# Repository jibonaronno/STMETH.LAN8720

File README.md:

# STM32ETH.LAN8720
Some standard library files has been customized for test board making simplyfication. A resistor footprint package 0204/7 from resistor.lbr is slightly modyfied.<br>
<br />

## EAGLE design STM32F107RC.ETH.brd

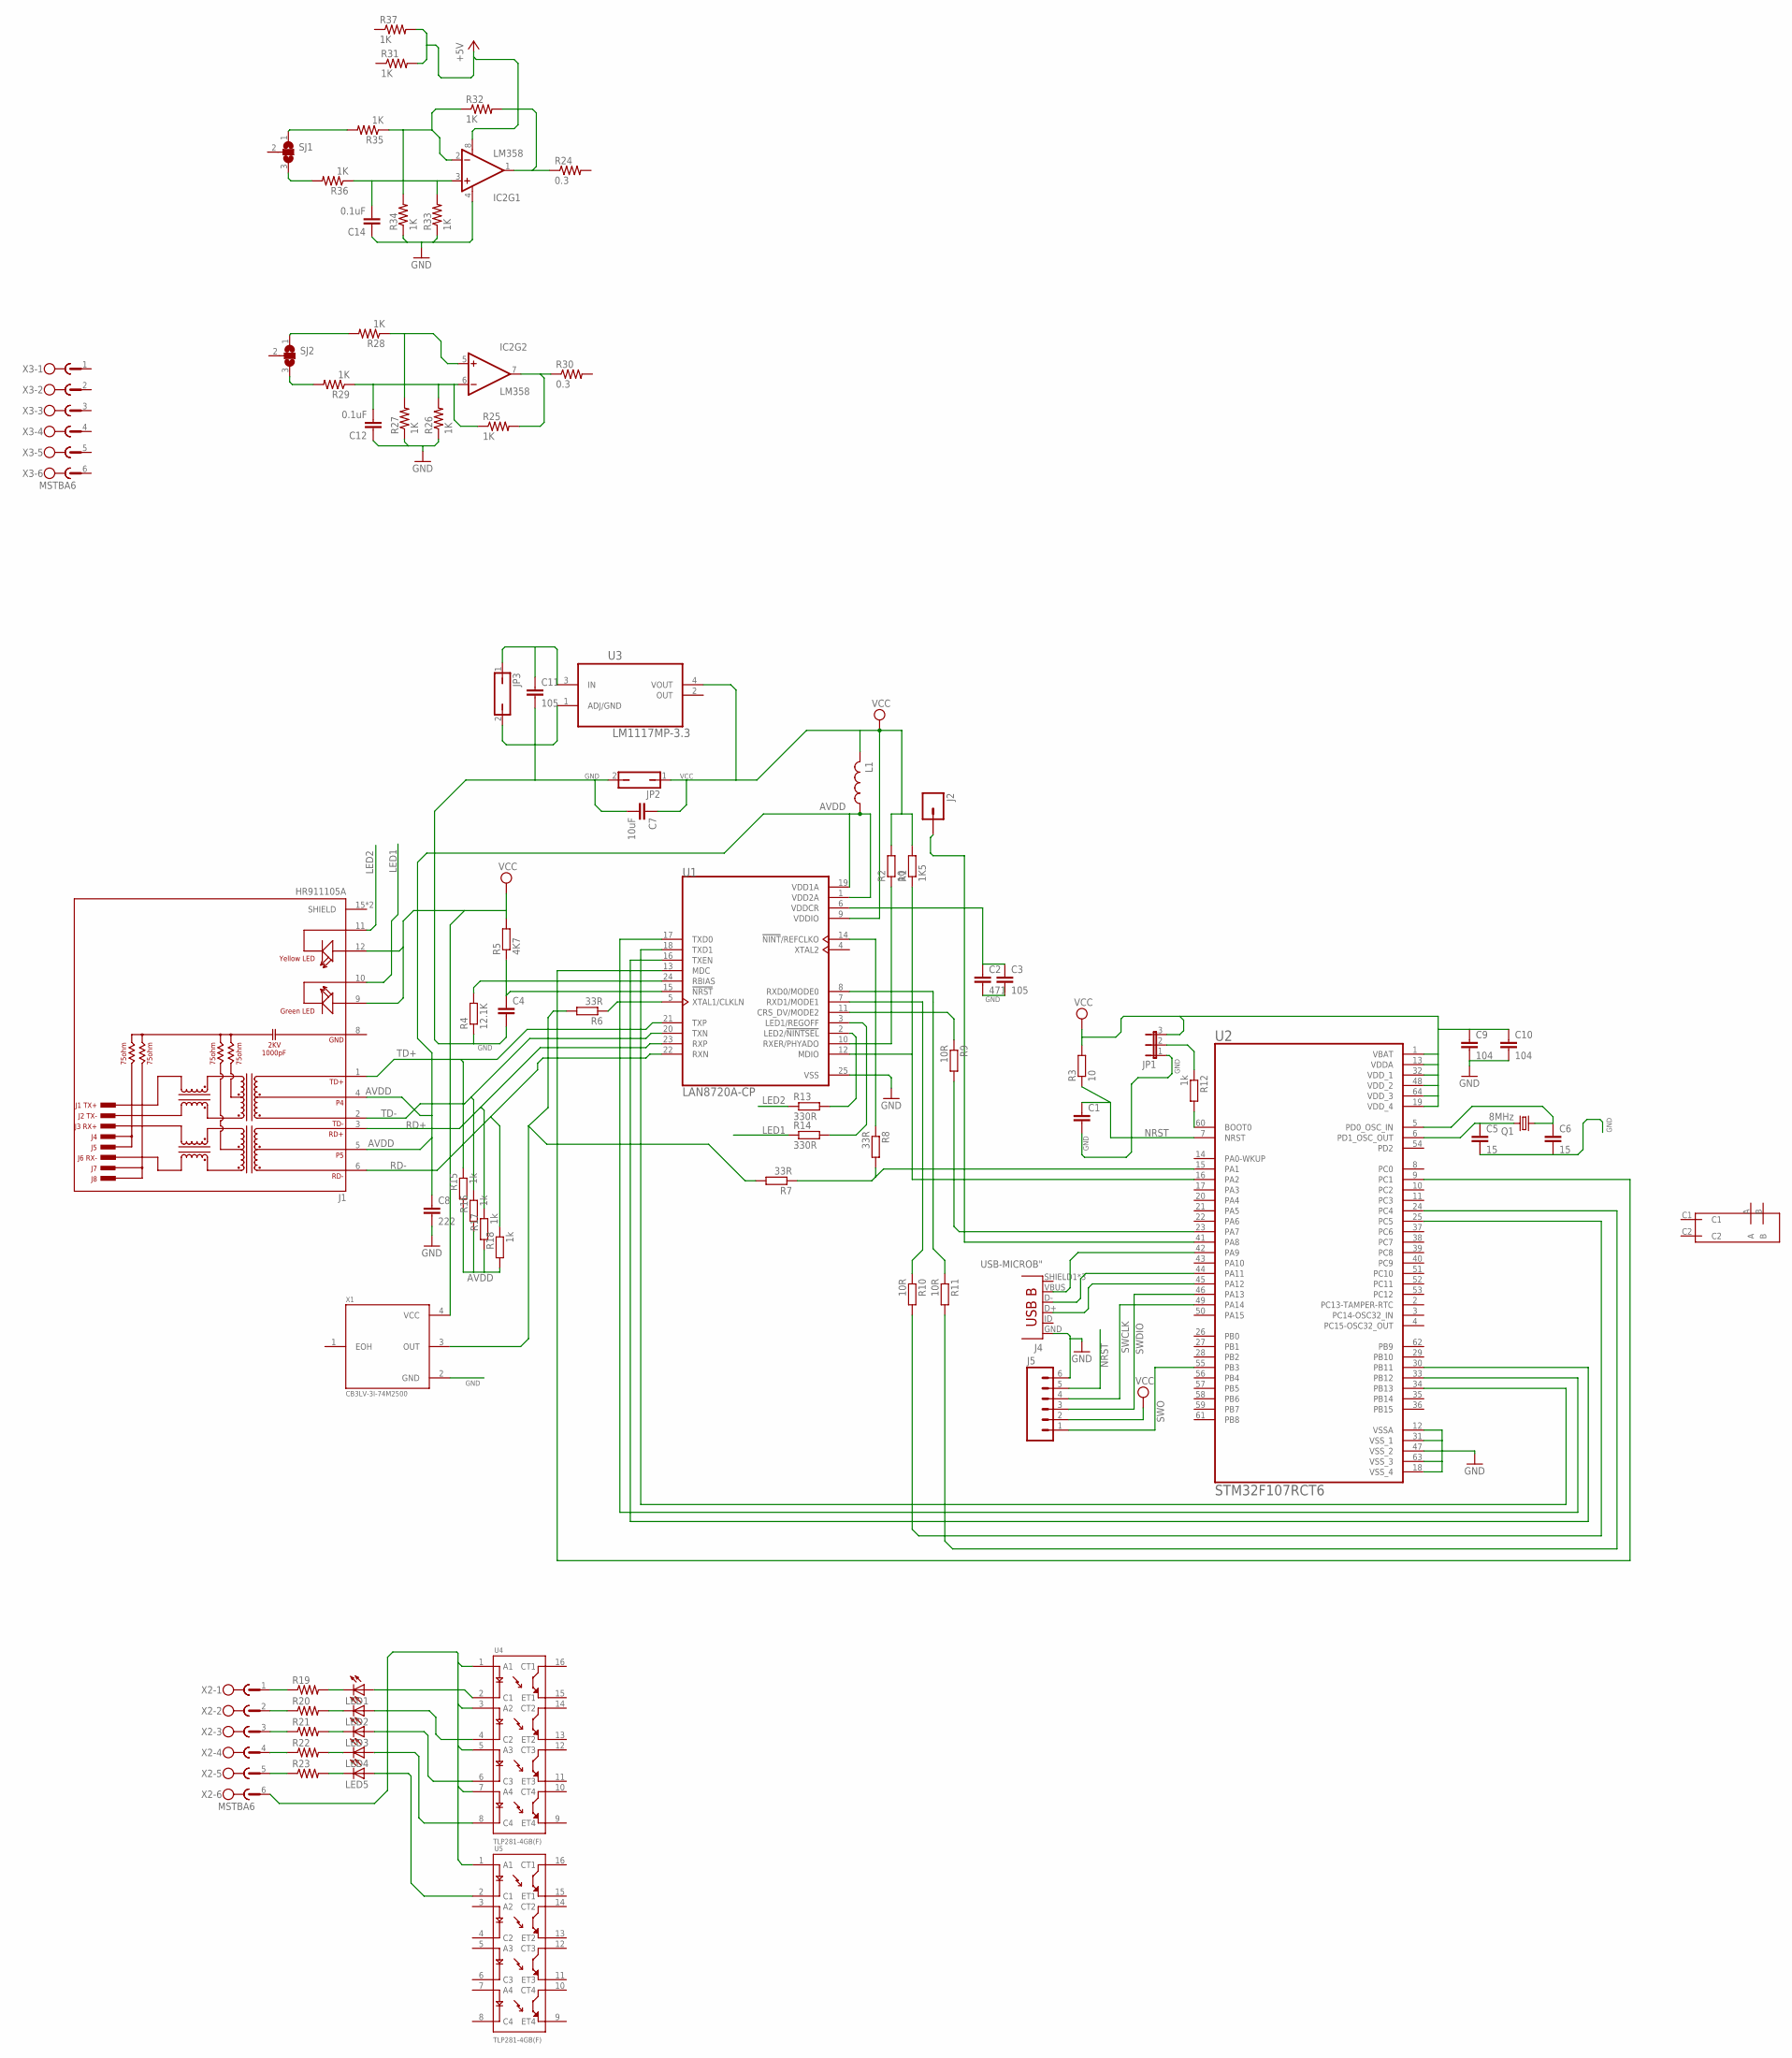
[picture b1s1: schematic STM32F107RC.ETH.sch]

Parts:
C1, C4: C-EUC1206; C1206
C2: 471; C1206
C3, C11: 105; C1206
C5, C6: 15; C1206
C7: 10uF; C1206
C8: 222; C1206
C9, C10: 104; C1206
C12, C14: 0.1uF; 0603-CAP
IC2: LM358; LM358_DIP08
J1: HR911105A; HANRUN_HR911105A
J2: M01OFFSET; 1X01_OFFSET
J4: USB-MICROB"; USB-B-MICRO-SMD_V03
J5: M06POLAR; MOLEX-1X6
JP1: JP2E; JP2
JP2, JP3: JP1Q; JP1
L1: L-US0207/7; 0207/7
LED1, LED2, LED3, LED4, LED5: LEDCHIPLED_0805; CHIPLED_0805
Q1: 8MHz; HC49/S
R1: 1K5; 0204/7
R2, R3: 10; 0204/7
R4: 12.1K; 0204/7
R5: 4K7; 0204/7
R6, R7, R8: 33R; 0204/7
R9, R10, R11: 10R; 0204/7
R12, R15, R16, R17, R18: 1k; 0204/7
R13, R14: 330R; 0204/7
R19, R20, R21, R22, R23: RESISTOR0805-RES; 0805
R24, R30: 0.3; 0805
R25, R26, R27, R28, R29, R31, R32, R33, R34, R35, R36, R37: 1K; AXIAL-0.3
SJ1, SJ2: SJ2W; SJ_2
U1: LAN8720A-CP; QFN50P400X400X100-25N
U2: STM32F107RCT6; QFP50P1200X1200X160-64N
U3: LM1117MP-3.3; SOT230P696X180-4N
U4, U5: TLP281-4GB(F); SOIC127P700X210-16N
U$1: OMRON-RELAY-G5NB; OMRON-G5NB
X1: CB3LV-3I-74M2500; OSCCC700X500X180-4N
X2, X3: MSTBA6

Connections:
+5V: IC2.8 (V+), R31.P$2 (2), R37.P$2 (2)
AVDD: C8.1, J1.4, J1.5, L1.1, R15.2, R16.2, R17.2, R18.2, U1.1 (VDD2A), U1.19 (VDD1A)
GND: C1.2, C2.2, C3.2, C4.2, C5.2, C6.2, C7.2, C8.2, C9.2, C10.2, C11.2, C12.1, C14.1, IC2.4 (V-), J1.8 (GND), J4.GND, J5.6, JP1.1, JP2.2, JP3.2, R4.1, R26.P$1 (1), R27.P$1 (1), R33.P$1 (1), R34.P$1 (1), U1.25 (VSS), U2.12 (VSSA), U2.18 (VSS_4), U2.31 (VSS_1), U2.47 (VSS_2), U2.63 (VSS_3), U3.1 (ADJ/GND), X1.2 (GND)
LED1: J1.10 (GC), R14.1
LED2: J1.11 (YC), R13.1
unnamed: R1.1, U1.12 (MDIO), U2.16 (PA2)
unnamed: U1.13 (MDC), U2.9 (PC1)
unnamed: R7.1, R8.2, U2.15 (PA1)
unnamed: R9.2, U2.23 (PA7)
unnamed: R11.2, U2.24 (PC4)
unnamed: J4.VBUS, U2.42 (PA9)
unnamed: U1.16 (TXEN), U2.30 (PB11)
unnamed: U1.17 (TXD0), U2.33 (PB12)
unnamed: U1.18 (TXD1), U2.34 (PB13)
unnamed: J2.1, U2.41 (PA8)
unnamed: J4.D-, U2.44 (PA11)
unnamed: R2.1, U1.10 (RXER/PHYADO)
unnamed: R4.2, U1.24 (RBIAS)
unnamed: C2.1, C3.1, U1.6 (VDDCR)
unnamed: R10.2, U2.25 (PC5)
unnamed: C4.1, R5.1, U1.15 (!NRST)
unnamed: R6.1, U1.5 (XTAL1/CLKLN)
unnamed: R6.2, R7.2, X1.3 (OUT)
unnamed: R8.1, U1.14 (!NINT!/REFCLKO)
unnamed: R9.1, U1.11 (CRS_DV/MODE2)
unnamed: R10.1, U1.7 (RXD1/MODE1)
unnamed: R11.1, U1.8 (RXD0/MODE0)
unnamed: C11.1, JP3.1, U3.3 (IN)
unnamed: JP1.2, R12.1
unnamed: R12.2, U2.60 (BOOT0)
unnamed: C6.1, Q1.1, U2.5 (PD0_OSC_IN)
unnamed: C5.1, Q1.2, U2.6 (PD1_OSC_OUT)
unnamed: J4.D+, U2.45 (PA12)
unnamed: R19.1, X2.1
unnamed: R20.1, X2.2
unnamed: R21.1, X2.3
unnamed: LED1.C, R19.2
unnamed: LED2.C, R20.2
unnamed: LED3.C, R21.2
unnamed: LED1.A, U4.2 (C1)
unnamed: LED2.A, U4.4 (C2)
unnamed: LED3.A, U4.6 (C3)
unnamed: U4.1 (A1), U4.3 (A2), U4.5 (A3), U4.7 (A4), U5.1 (A1), X2.6
unnamed: R22.1, X2.4
unnamed: LED4.C, R22.2
unnamed: LED4.A, U4.8 (C4)
unnamed: C12.2, IC2.6 (-IN), R25.P$1 (1), R26.P$2 (2), R29.P$1 (1)
unnamed: R23.1, X2.5
unnamed: LED5.C, R23.2
unnamed: LED5.A, U5.2 (C1)
unnamed: IC2.5 (+IN), R27.P$2 (2), R28.P$1 (1)
unnamed: IC2.7 (OUT), R25.P$2 (2), R30.1
unnamed: R28.P$2 (2), SJ2.1
unnamed: R29.P$2 (2), SJ2.3
unnamed: IC2.2 (-IN), R32.P$1 (1), R34.P$2 (2), R35.P$1 (1)
unnamed: C14.2, IC2.3 (+IN), R33.P$2 (2), R36.P$1 (1)
unnamed: IC2.1 (OUT), R24.1, R32.P$2 (2)
unnamed: R35.P$2 (2), SJ1.1
unnamed: R36.P$2 (2), SJ1.3
NRST: C1.1, J5.5, R3.1, U2.7 (NRST)
RD+: J1.3 (RD+), R17.1, U1.23 (RXP)
RD-: J1.6 (RD-), R18.1, U1.22 (RXN)
SIG_LED01: R14.2, U1.3 (LED1/REGOFF)
SIG_LED02: R13.2, U1.2 (LED2/!NINTSEL!)
SWCLK: J5.4, U2.49 (PA14)
SWDIO: J5.3, U2.46 (PA13)
SWO: J5.1, U2.55 (PB3)
TD+: J1.1 (TD+), R15.1, U1.21 (TXP)
TD-: J1.2 (TD-), R16.1, U1.20 (TXN)
VCC: C7.1, C9.1, C10.1, J1.9 (GA), J1.12 (YA), J5.2, JP1.3, JP2.1, L1.2, R1.2, R2.2, R3.2, R5.2, U1.9 (VDDIO), U2.1 (VBAT), U2.13 (VDDA), U2.19 (VDD_4), U2.32 (VDD_1), U2.48 (VDD_2), U2.64 (VDD_3), U3.4 (VOUT), X1.4 (VCC)

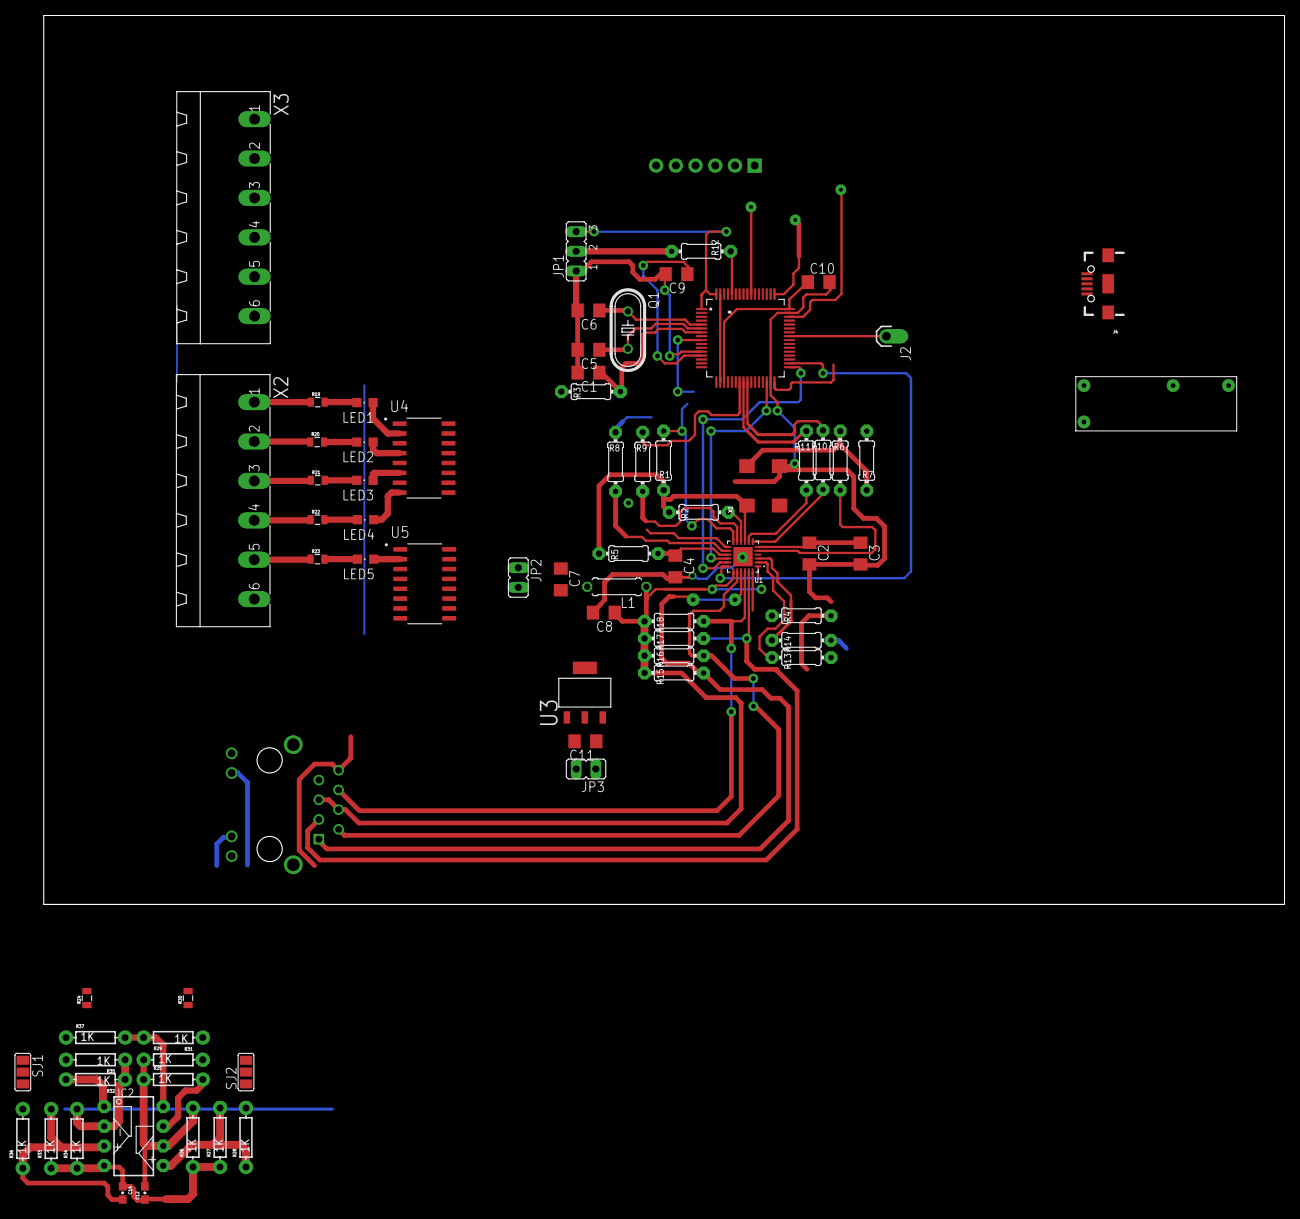
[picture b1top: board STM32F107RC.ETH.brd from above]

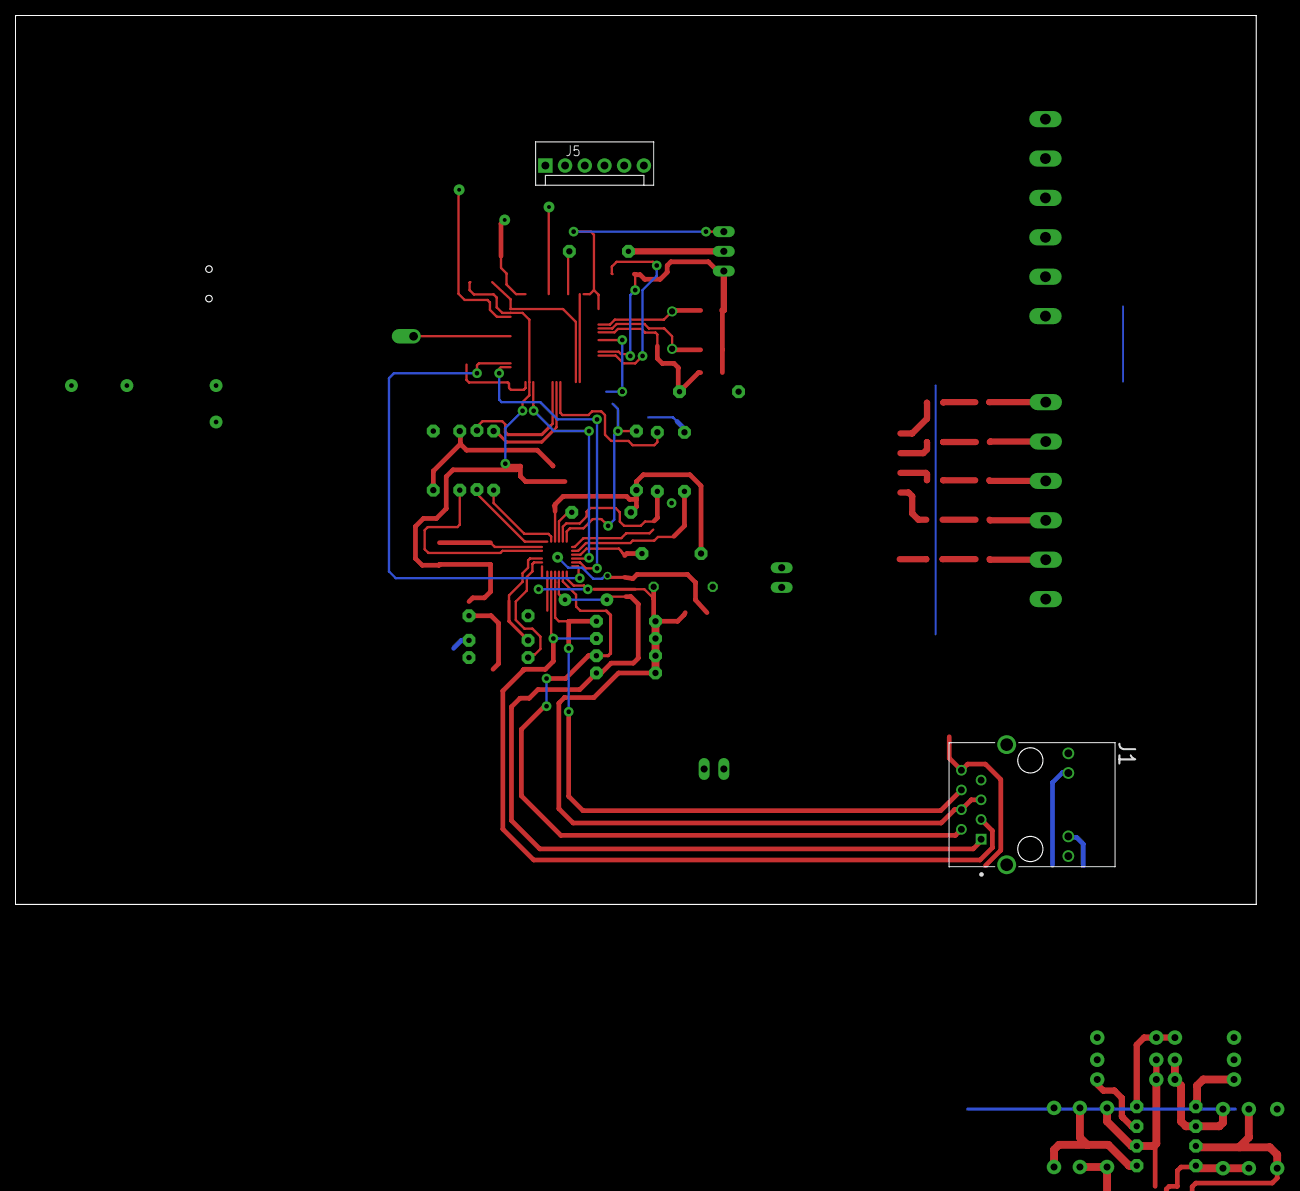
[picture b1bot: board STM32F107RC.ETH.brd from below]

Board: 2 copper layers, 160.0 x 114.6 mm, 76 parts (2 on the bottom side), 70 nets.

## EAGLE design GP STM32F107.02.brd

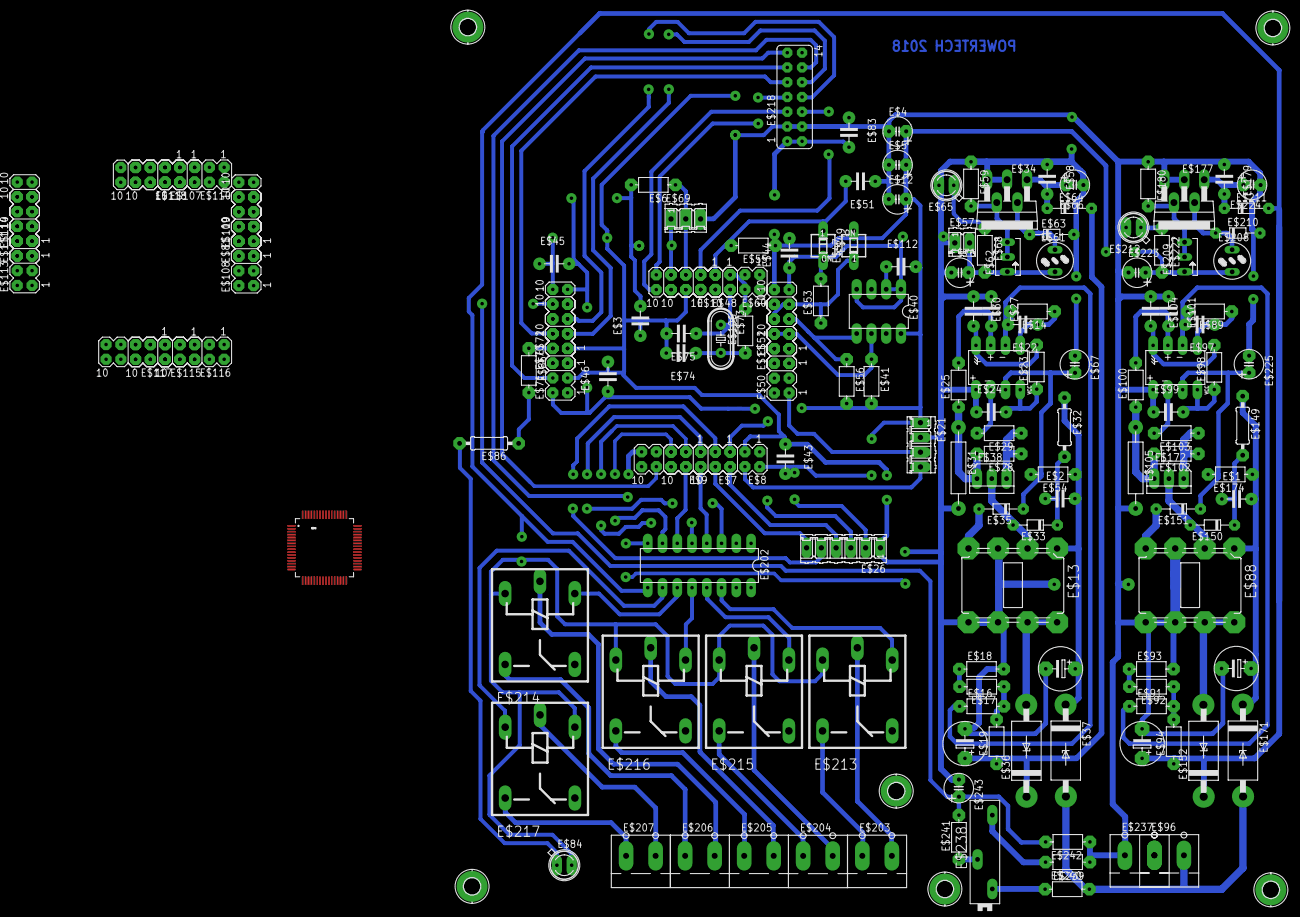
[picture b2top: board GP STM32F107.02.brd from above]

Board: 2 copper layers, 157 parts (0 on the bottom side), 97 nets.

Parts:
E$1, E$2, E$3, E$22, E$24, E$27, E$30, E$43, E$44, E$45, E$46, E$51, E$58, E$74, E$75, E$83, E$97, E$99, E$101, E$104, E$112, E$179: C5
E$4, E$5, E$12, E$66, E$67, E$76, E$223, E$224, E$225, E$243: C2.5-2
E$6, E$14, E$16, E$17, E$18, E$19, E$23, E$25, E$28, E$29, E$41, E$53, E$54, E$55, E$56, E$59, E$68, E$85, E$89, E$91, E$92, E$93, E$94, E$98, E$100, E$102, E$103, E$106, E$174, E$180, E$222, E$239, E$240, E$241, E$242: R7-5
E$7, E$8, E$9, E$10, E$11, E$48, E$50, E$52, E$60, E$70, E$71, E$72, E$81, E$107, E$108, E$109, E$110, E$111, E$113, E$114, E$115, E$116, E$117, E$118: MA05-2
E$13, E$88: INDUCTOR_MEDIUM
E$15, E$90: DIL08
E$20, E$39, E$95, E$173: ES-5
E$21: 04P
E$26: 06P
E$31, E$105: R1_5W
E$32, E$86, E$149: 0207/10
E$33, E$35, E$63, E$64, E$150, E$151, E$210, E$211: D-5
E$34, E$177: L200S
E$36, E$37, E$152, E$171: CB429-17
E$38, E$172: TO92-BCE
E$40: AT24C512
E$42: QFP50P1200X1200X160-64N
E$47, E$49: SD4-01
E$57: 02P
E$61, E$208: 82114R
E$62, E$209: B64Y
E$65, E$84, E$212: SFH480
E$69: 03P
E$73: HC49/S
E$77, E$78, E$79, E$80, E$82, E$87: 2,8-PAD
E$96, E$203, E$204, E$205, E$206, E$207, E$237: CONNECTOR-AWG-14-24
E$202: DIL16
E$213, E$214, E$215, E$216, E$217: ZF112
E$218: FE07-2
E$238: PT-SPIN

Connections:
S$6: E$11.6, E$40.6, E$41.1
S$7: E$11.8, E$47.1, E$53.1
S$9: E$70.4, E$85.1
S$11: E$48.1, E$106.2
S$12: E$3.P$5, E$4.1, E$5.1, E$8.3, E$12.1, E$13.3, E$13.4, E$13.8, E$15.5, E$18.2, E$20.2, E$21.2, E$24.P$5, E$26.1, E$27.P$5, E$30.P$5, E$31.P$4, E$34.3, E$34.5, E$39.2, E$40.1, E$40.2, E$40.4, E$43.P$5, E$44.P$5, E$45.P$5, E$46.P$4, E$48.8, E$49.2, E$51.P$5, E$52.9, E$53.2, E$57.1, E$58.P$5, E$59.1, E$63.A, E$65.A, E$66.1, E$67.1, E$69.3, E$70.3, E$71.3, E$72.10, E$74.P$4, E$75.P$4, E$76.1, E$83.P$5, E$88.3, E$88.4, E$88.8, E$90.5, E$93.2, E$95.2, E$99.P$5, E$101.P$5, E$104.P$5, E$105.P$4, E$112.P$5, E$173.2, E$177.3, E$177.5, E$179.P$5, E$180.1, E$202.8, E$210.A, E$212.A, E$218.3, E$218.4, E$223.1, E$224.1, E$225.1, E$237.P$2, E$240.1, E$242.1, E$243.1
S$14: E$6.1, E$48.7, E$69.2
S$30: E$48.5, E$218.6
S$33: E$203.P$3, E$213.P
S$39: E$3.P$4, E$4.2, E$5.2, E$6.2, E$8.2, E$12.2, E$21.1, E$26.2, E$40.8, E$41.2, E$43.P$4, E$44.P$4, E$45.P$4, E$46.P$5, E$47.2, E$48.9, E$52.10, E$55.1, E$56.2, E$69.1, E$71.2, E$72.9, E$83.P$4, E$112.P$4, E$208.2, E$209.E, E$218.1, E$218.2, E$222.2, E$223.2
S$41: E$202.10, E$217.2
S$43: E$21.3, E$50.1
S$44: E$85.2, E$86.1
S$50: E$7.4, E$26.6
S$55: E$73.2, E$74.P$5, E$106.1
S$57: E$11.7, E$40.5, E$56.1
S$60: E$84.K, E$86.2
S$61: E$2.P$4, E$13.5, E$20.1, E$32.1, E$37.C, E$54.1
S$63: E$48.2, E$73.1, E$75.P$5
S$65: E$70.10, E$241.2, E$242.2, E$243.2
S$67: E$48.3, E$49.1, E$51.P$4, E$55.2
S$128: E$70.6, E$218.9
S$133: E$15.3, E$25.2, E$27.P$4
S$134: E$15.4, E$23.2, E$30.P$4
S$135: E$15.8, E$23.1, E$24.P$4
S$136: E$15.6, E$29.2
S$139: E$28.1, E$29.1, E$38.B
S$145: E$17.2, E$18.1
S$150: E$16.2, E$17.1, E$19.2
S$151: E$14.1, E$15.1, E$22.P$5
S$153: E$14.2, E$15.2, E$16.1, E$22.P$4
S$155: E$13.2, E$13.6, E$36.A
S$156: E$25.1, E$28.2, E$31.P$3, E$38.E
S$157: E$2.P$5, E$32.2, E$33.C
S$158: E$13.1, E$33.A, E$38.C
S$161: E$15.7, E$35.C, E$54.2, E$67.2
S$163: E$13.7, E$35.A
S$164: E$1.P$4, E$88.5, E$95.1, E$149.1, E$171.C, E$174.1
S$166: E$70.5, E$218.10
S$171: E$71.4, E$218.11
S$189: E$7.1, E$26.3
S$210: E$34.1, E$58.P$4, E$64.C, E$66.2
S$211: E$34.4, E$59.2, E$62.A, E$62.S
S$215: E$57.2, E$61.2, E$62.E, E$68.2, E$76.2
S$217: E$34.2, E$61.1, E$63.C
S$224: E$65.K, E$68.1
S$226: E$90.3, E$100.2, E$101.P$4
S$227: E$8.4, E$21.4
S$228: E$19.1, E$36.C, E$39.1, E$64.A
S$231: E$7.7, E$202.5
S$234: E$7.8, E$202.6
S$236: E$7.5, E$202.3
S$238: E$7.9, E$202.7
S$239: E$90.4, E$98.2, E$104.P$4
S$240: E$90.8, E$98.1, E$99.P$4
S$241: E$90.6, E$103.2
S$242: E$7.3, E$26.5
S$243: E$7.6, E$202.4
S$247: E$102.1, E$103.1, E$172.B
S$253: E$7.2, E$26.4
S$266: E$92.2, E$93.1
S$267: E$91.2, E$92.1, E$94.2
S$268: E$89.1, E$90.1, E$97.P$5
S$269: E$89.2, E$90.2, E$91.1, E$97.P$4
S$270: E$88.2, E$88.6, E$152.A
S$271: E$100.1, E$102.2, E$105.P$3, E$172.E
S$272: E$1.P$5, E$149.2, E$150.C
S$278: E$88.1, E$150.A, E$172.C
S$281: E$90.7, E$151.C, E$174.2, E$225.2
S$301: E$88.7, E$151.A
S$325: E$202.11, E$214.1
S$326: E$202.12, E$216.1
S$332: E$202.14, E$213.1
S$333: E$202.13, E$215.1
S$334: E$203.P$2, E$213.S
S$335: E$204.P$2, E$215.S
S$336: E$205.P$2, E$216.S
S$337: E$205.P$3, E$216.P
S$338: E$207.P$2, E$217.S
S$341: E$204.P$3, E$215.P
S$342: E$207.P$3, E$217.P
S$345: E$206.P$2, E$214.S
S$354: E$177.1, E$179.P$4, E$211.C, E$224.2
S$358: E$177.4, E$180.2, E$209.A, E$209.S
S$365: E$9.8, E$218.13
S$368: E$9.9, E$218.12
S$370: E$70.7, E$218.8
S$373: E$10.9, E$218.7
S$374: E$10.10, E$218.5
S$375: E$177.2, E$208.1, E$210.C
S$378: E$206.P$3, E$214.P
S$381: E$212.K, E$222.1
S$382: E$84.A, E$202.9, E$211.A, E$213.2, E$214.2, E$215.2, E$216.2, E$217.1
S$383: E$94.1, E$152.C, E$173.1
S$390: E$37.A, E$96.P$3, E$171.A, E$239.2
S$392: E$238.A, E$239.1
S$393: E$238.E, E$240.2
S$394: E$238.S, E$241.1

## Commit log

2018-11-01 commit 002
2018-11-02 desktop update
2018-11-02 u from surface
2018-11-04 lenovo up
2018-11-04 5.11.18
2018-11-05 6.11.18
2018-11-06 u 6.11.18
2018-11-08 u 9-11-18
2018-11-09 u 10-11-18
2018-11-09 u 10-11-18 added USB OPTO INPUT;
2018-11-12 u 12-11-18
2018-11-12 omron relay library added. 12-11-18
2018-11-28 u 11/28/18
2018-11-30 U01.12.18

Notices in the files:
parts and their libraries:
SparkFun-Connectors: Licensing: Creative Commons ShareAlike 4.0 International - https://creativecommons.org/licenses/by-sa/4.0
